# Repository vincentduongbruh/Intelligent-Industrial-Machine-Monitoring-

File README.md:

# Intelligent Industrial Motor Monitoring

**Real-Time Fault Detection Using Current, Vibration, and Temperature Sensing**

This project presents an intelligent motor health monitoring system designed to detect early-stage electrical and mechanical faults in industrial motors. The system continuously measures **3-phase current**, **vibration**, and **temperature**, analyzes these signals in real time, and visualizes motor health indicators through a graphical user interface (GUI).

The work was conducted in collaboration with **NASA Ames Research Center** and builds upon prior research on generalized fault detection using the **Filtered Park’s Vector Approach (FPVA)**. While traditional fault-detection methods often remain confined to offline analysis or simulation, this project focuses on a **deployable, sensor-driven monitoring platform** suitable for real-world industrial environments.

---

## Motivation

Induction motors account for approximately **90% of electrically driven industrial machinery**, including:
- Manufacturing robots
- CNC machines
- Conveyors
- HVAC systems
- Aerospace actuators and pumps

Despite their ubiquity, motor faults such as **bearing wear**, **shaft misalignment**, **gear damage**, and **electrical phase imbalance** often go undetected until catastrophic failure. These faults manifest as changes in:
- Current signatures
- Vibration spectra
- Operating temperature

This project bridges the gap between **fault-detection algorithms** and **physical monitoring infrastructure**, enabling early detection and improved system reliability.

---

## System Overview

The system is composed of three primary subsystems:

1. **Temperature & Vibration Sensing PCB**
2. **3-Phase Current Sensing PCB**
3. **Data Processing Server and GUI**

Sensor data is transmitted to the processing server via a combination of **USB** and **Bluetooth Low Energy (BLE)** links.

> Note: Due to limited access to industrial induction motors, testing was performed using **ESC-driven brushless motors**. While this changes the expected current waveforms, the monitoring approach remains applicable to industrial motors and VFD-driven systems.

---

## Hardware Architecture

### Sensors
- **Temperature**: Dual SHT30 temperature sensors mounted near motor windings
- **Vibration**: Dual MPU6500 IMUs measuring linear acceleration
- **Current**: Non-invasive current transformer measuring 3-phase current

### Electronics
- **ESP32 Microcontrollers**
  - One ESP32 for temperature & vibration sensing
  - One ESP32 for high-speed current acquisition

### Physical Testing Rig
- Custom **3D-printed rig** for:
  - Mechanical stability
  - Consistent sensor placement
  - Repeatable experiments

---

## Embedded Software

### Sensor Drivers
- Custom I2C drivers for temperature and IMU sensors
- Register-level configuration based on manufacturer datasheets
- Real-time data acquisition

### Sensor Calibration
- **Affine sensor model** used to correct bias and sensitivity
- Gravity-based calibration for IMUs
- Known-reference calibration for temperature sensors

### Signal Conditioning
- **Exponential Moving Average (EMA) low-pass filtering**
  - Reduces high-frequency noise
  - Lightweight and suitable for real-time embedded systems

### Communication
- **BLE (1 kHz)**: Temperature and vibration data
- **USB (10 kHz)**: Phase-accurate 3-phase current data
  - Chosen to avoid wireless latency and phase misalignment

---

## Data Processing

### Park’s Vector Approach
- Converts 3-phase currents into the rotating **d–q reference frame**
- Enables fault detection through geometric patterns in the id–iq plane

Under ideal conditions:
- Healthy motor → circular Park’s Vector trajectory
- Faulted motor → distorted or asymmetric trajectory

For ESC-driven motors:
- Healthy motor → six-pointed star pattern
- Phase fault → collapsed or triangular pattern

The system adapts the interpretation of Park’s Vector results based on the motor drive method.

---

## Graphical User Interface (GUI)

The GUI provides real-time visualization of:

1. **3-Phase Current Waveforms**
2. **Filtered Park’s Vector Plot**
3. **Vibration (Time + Frequency Domain)**
   - RMS vibration
   - FFT-based frequency analysis
4. **Temperature Monitoring**

Threshold-based alerts notify the user of potential electrical or mechanical faults.

---

## Testing and Validation

Fault conditions were intentionally introduced to validate system behavior:
- **Phase imbalance** via diode-induced waveform distortion
- **Mechanical vibration** using off-center rotating loads
- **Thermal stress** via high-throttle motor operation

The system consistently distinguished healthy and faulted operating states across current, vibration, and temperature modalities.

---

## Challenges and Limitations

- **Wireless latency** caused phase misalignment (resolved by USB current transmission)
- **ESC-driven motors** produce non-sinusoidal waveforms
- **High sampling rates** (≥10 kHz) required for accurate current analysis
- Limited access to industrial induction motors for final validation

---

## Future Work

- Deploy and validate system on industrial induction motors
- Apply machine learning for **multi-class fault classification**
- Extract higher-level features from current, vibration, and thermal data
- Improve fault localization and severity estimation

---

## Team

- **Nick Bui**
- **Mohamed Homsi**
- **Aashrith Beesabathuni**
- **Vincent Duong**
- **Carter Chen**

---

## Acknowledgements

We thank:
- Professor Dutta
- Paul De La Sayette
- Matteo Guarrera
- Dr. Rodney Martin
- Isak Bolin (NASA Ames Research Center)

for their guidance and foundational research support.

---

## References

- Bolin, I. *Generalized Fault Detection of Broken Rotor Bars in Induction Motors*, Uppsala University, 2024.

---

## To run GUI on Raspberry Pi or Laptop: 
<pre>cd src/raspberry_pi </pre>
<pre>python -m venv env</pre>
<pre>source env/bin/activate</pre>
<pre>pip install -r requirements.txt</pre>
<pre>python gui.py</pre>

## Troubleshooting FAQ:
#### BLE Connection Failing: 
- Ctrl+C to terminate
- Reset ESP 1
- <pre>python gui.py</pre>
#### CT Data Missing:
- Ctrl+C to terminate
- Reset ESP2
- <pre>python gui.py</pre>

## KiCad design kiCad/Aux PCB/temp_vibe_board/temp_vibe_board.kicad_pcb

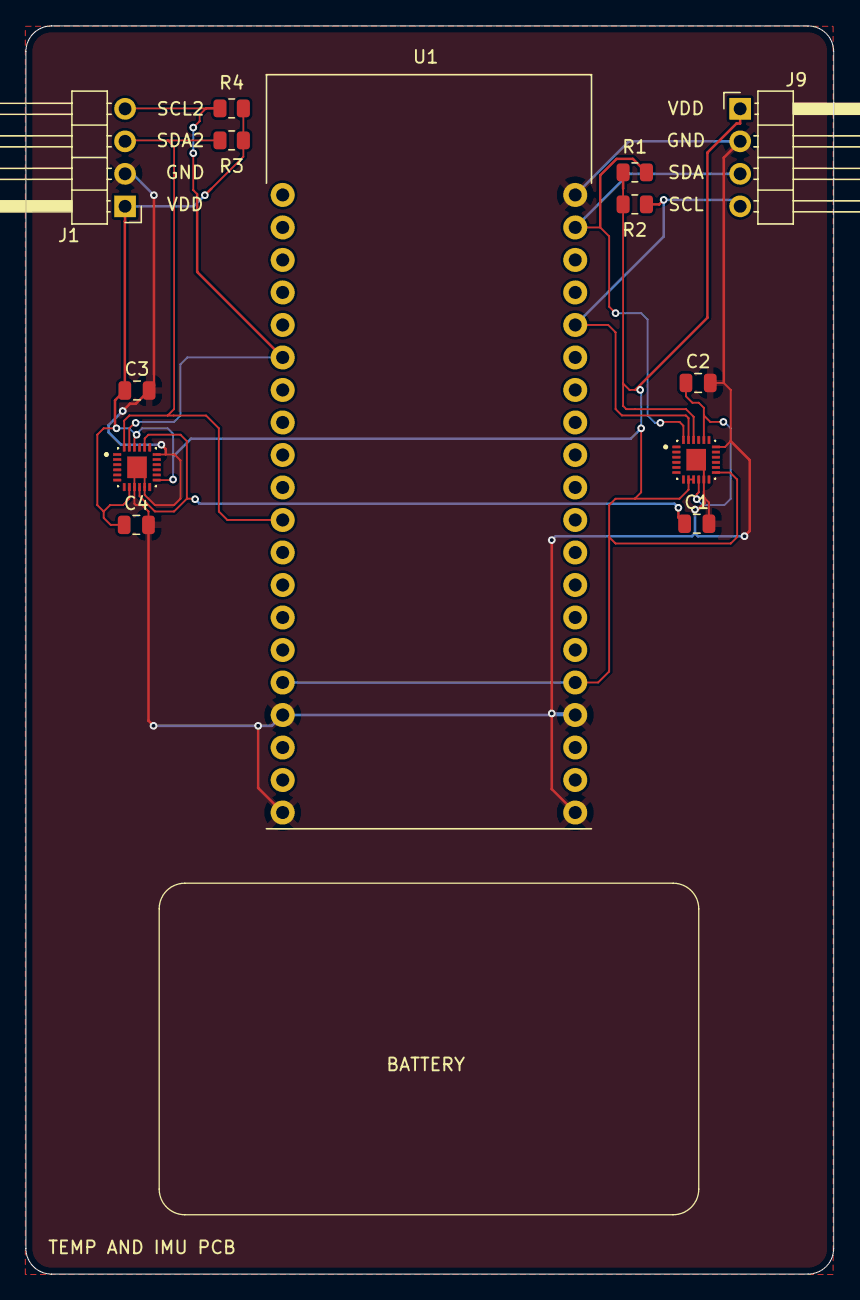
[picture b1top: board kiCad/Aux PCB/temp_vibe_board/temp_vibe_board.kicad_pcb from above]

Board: 2 copper layers, 63.1 x 97.5 mm, 13 parts (0 on the bottom side), 8 nets.

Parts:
C1, C2, C3, C4: 0.1 uF; C_0805_2012Metric
J1, J9: Conn_01x04_Pin; PinHeader_1x04_P2.54mm_Horizontal
R1, R2, R3, R4: 4.7 K; R_0805_2012Metric
U1: DEV-13907; MODULE_DEV-13907
U2, U6: MPU-6500; MPU6500

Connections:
GND: C1.2, C2.2, C3.2, C4.2, J1.2, J9.2, U1.J1_1 (GND), U1.J1_4 (GND), U1.J2_1 (GND), U1.J2_4 (GND), U1.J2_20 (GND), U2.11 (FSYNC), U2.18 (GND), U2.25 (EXP), U6.9 (AD0/SDO), U6.11 (FSYNC), U6.18 (GND), U6.25 (EXP)
unnamed: C2.1, U2.10 (REGOUT), U2.20 (RESV_2)
unnamed: C1.1, U6.10 (REGOUT), U6.20 (RESV_2)
SCL: J9.4, R1.2, U1.J2_16 (U0_RTS/V_SPI_WP/GPIO22/SCL/22), U2.23 (SCL/SCLK)
SCL2: J1.4, R4.2, U1.J1_15 (TOUCH8/ADC1_5/GPIO33/XTAL32/33), U6.23 (SCL/SCLK)
SDA: J9.3, R2.2, U1.J2_19 (V_SPI_HD/GPIO21/SDA/21), U2.24 (SDA/SDI)
SDA2: J1.3, R3.2, U1.J1_10 (TOUCH7/ADC2_7/GPIO27/27), U6.24 (SDA/SDI)
VDDIO: C3.1, C4.1, J1.1, J9.1, R1.1, R2.1, R3.1, R4.1, U1.J1_5 (3.3V/3V3), U1.J2_5 (3.3V/3V3), U2.8 (VDDIO), U2.9 (AD0/SDO), U2.13 (VDD), U2.22 (NCS), U6.8 (VDDIO), U6.13 (VDD), U6.22 (NCS)

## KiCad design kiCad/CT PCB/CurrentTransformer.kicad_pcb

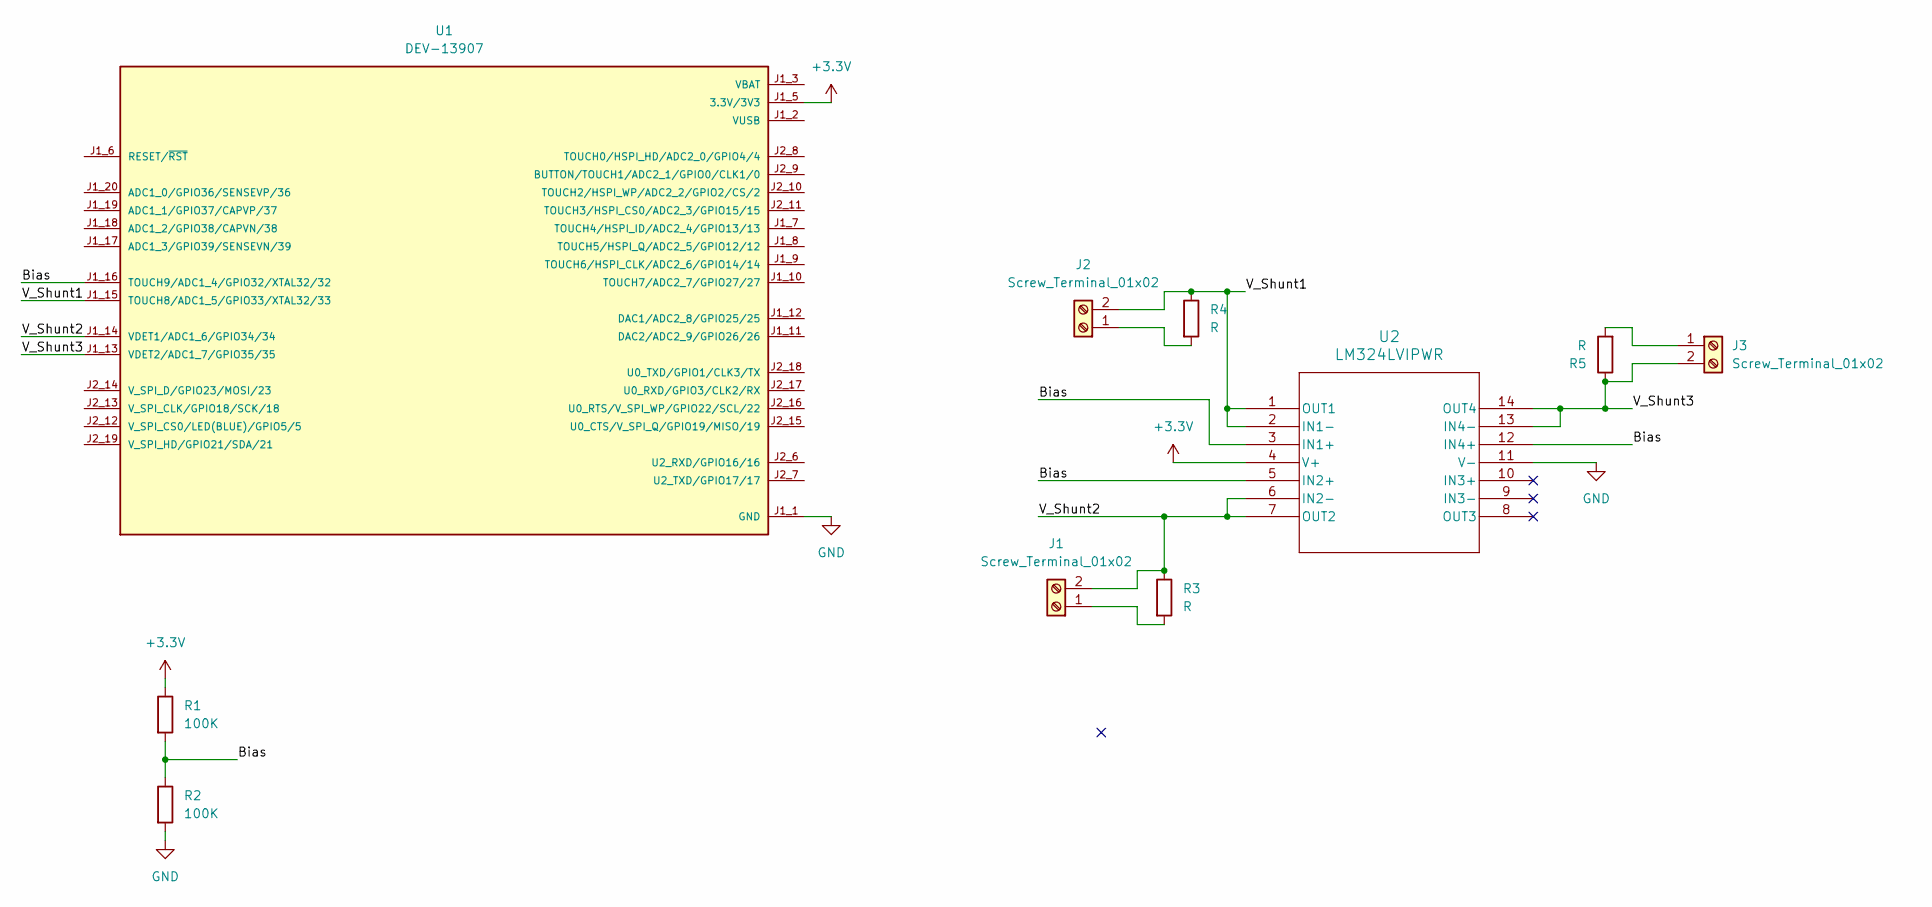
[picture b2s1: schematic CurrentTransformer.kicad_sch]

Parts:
J1, J2, J3: Screw_Terminal_01x02; OST_OSTTE020104
R1, R2: 100K; R_0603_1608Metric
R3, R4, R5: R; R_Axial_DIN0207_L6.3mm_D2.5mm_P10.16mm_Horizontal
U1: DEV-13907; MODULE_DEV-13907; PARTREV V10
U2: LM324LVIPWR; PW14_TEX-L

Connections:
+3.3V: R1.1, U1.J1_5 (3.3V/3V3), U1.J2_5 (3.3V/3V3), U2.4 (V+)
/Bias: R1.2, R2.1, U1.J1_16 (TOUCH9/ADC1_4/GPIO32/XTAL32/32), U2.3 (IN1+), U2.5 (IN2+), U2.12 (IN4+)
/V_Shunt1: J2.2, R4.1, U1.J1_15 (TOUCH8/ADC1_5/GPIO33/XTAL32/33), U2.1 (OUT1), U2.2 (IN1-)
/V_Shunt2: J1.2, R3.1, U1.J1_14 (VDET1/ADC1_6/GPIO34/34), U2.6 (IN2-), U2.7 (OUT2)
/V_Shunt3: J3.2, R5.1, U1.J1_13 (VDET2/ADC1_7/GPIO35/35), U2.13 (IN4-), U2.14 (OUT4)
GND: R2.2, U1.J1_1 (GND), U1.J1_4 (GND), U1.J2_1 (GND), U1.J2_4 (GND), U1.J2_20 (GND), U2.11 (V-)
unnamed: J1.1, R3.2
unnamed: J2.1, R4.2
unnamed: J3.1, R5.2
VBAT: U1.J1_3 (VBAT), U1.J2_3 (VBAT)
VUSB: U1.J1_2 (VUSB), U1.J2_2 (VUSB)

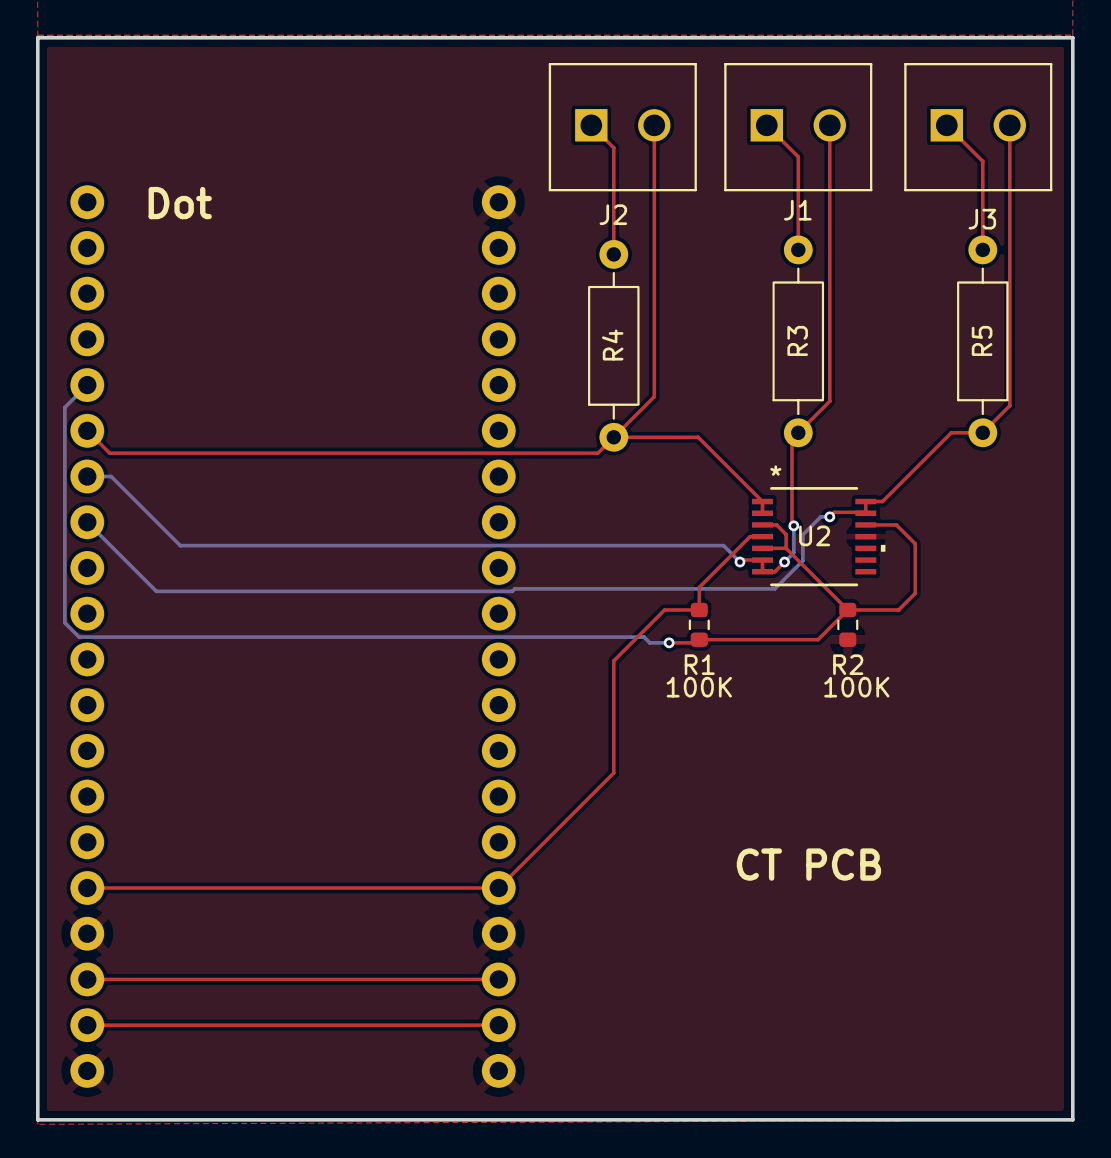
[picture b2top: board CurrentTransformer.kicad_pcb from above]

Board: 2 copper layers, 57.5 x 60.1 mm, 10 parts (1 on the bottom side), 11 nets.

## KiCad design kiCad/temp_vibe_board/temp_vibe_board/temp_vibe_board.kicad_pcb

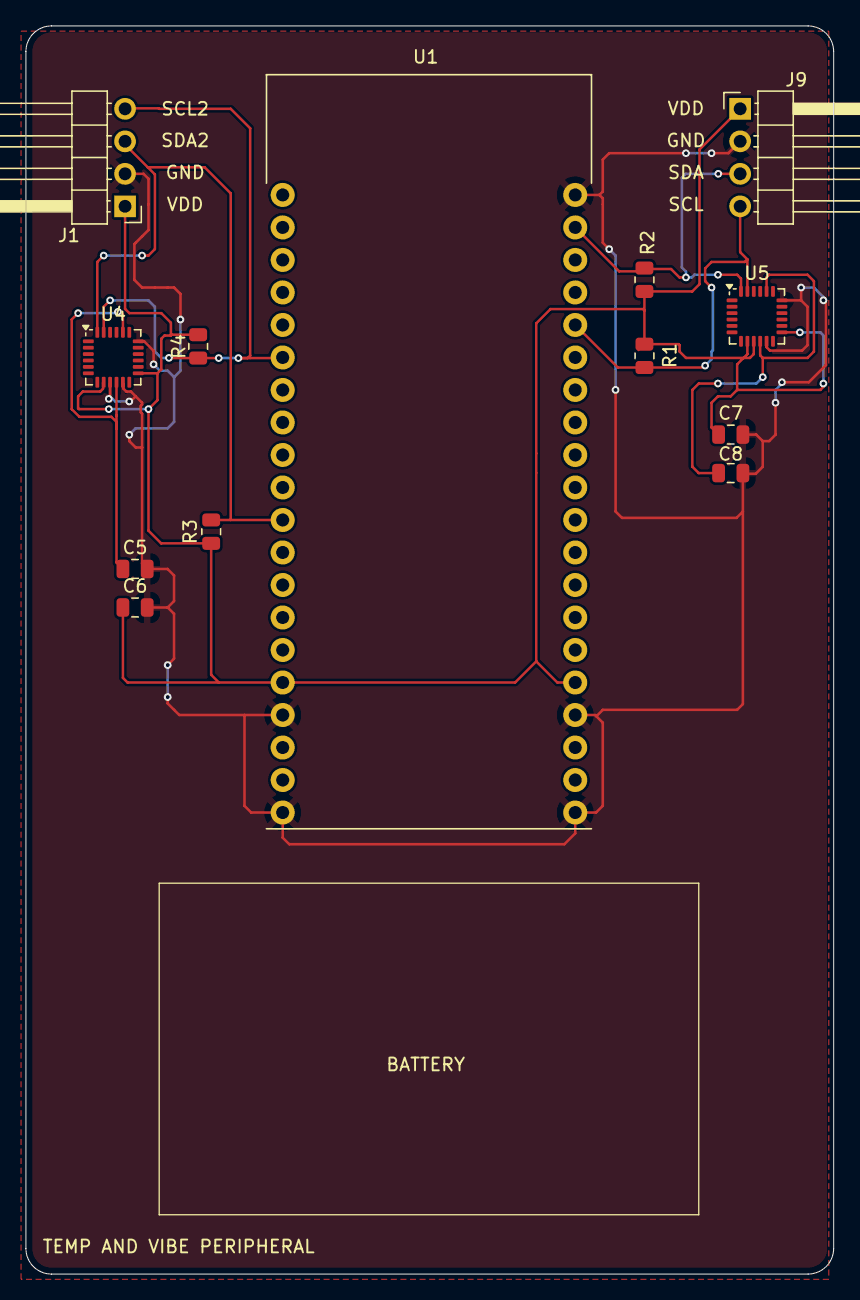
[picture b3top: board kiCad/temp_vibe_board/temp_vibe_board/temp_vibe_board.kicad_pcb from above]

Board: 2 copper layers, 63.1 x 97.5 mm, 13 parts (0 on the bottom side), 8 nets.

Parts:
C5, C6, C7, C8: 0.1 uF; C_0805_2012Metric
J1, J9: Conn_01x04_Pin; PinHeader_1x04_P2.54mm_Horizontal
R1, R2, R3, R4: 4.7 K; R_0805_2012Metric
U1: DEV-13907; MODULE_DEV-13907
U4, U5: MPU-6050; InvenSense_QFN-24_4x4mm_P0.5mm

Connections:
GND: C5.2, C6.2, C7.2, C8.2, J1.2, J9.2, U1.J1_1 (GND), U1.J1_4 (GND), U1.J2_1 (GND), U1.J2_4 (GND), U1.J2_20 (GND), U4.9 (AD0), U4.11 (FSYNC), U4.18 (GND), U5.11 (FSYNC), U5.18 (GND)
unnamed: C5.1, U4.10 (REGOUT), U4.20 (CPOUT)
unnamed: C8.1, U5.10 (REGOUT), U5.20 (CPOUT)
SCL: J9.4, R1.2, U1.J2_16 (U0_RTS/V_SPI_WP/GPIO22/SCL/22), U5.23 (SCL)
SCL2: J1.4, R4.2, U1.J1_15 (TOUCH8/ADC1_5/GPIO33/XTAL32/33), U4.23 (SCL)
SDA: J9.3, R2.2, U1.J2_19 (V_SPI_HD/GPIO21/SDA/21), U5.24 (SDA)
SDA2: J1.3, R3.2, U1.J1_10 (TOUCH7/ADC2_7/GPIO27/27), U4.24 (SDA)
VDDIO: C6.1, C7.1, J1.1, J9.1, R1.1, R2.1, R3.1, R4.1, U1.J1_5 (3.3V/3V3), U1.J2_5 (3.3V/3V3), U4.8 (VLOGIC), U4.13 (VDD), U5.8 (VLOGIC), U5.9 (AD0), U5.13 (VDD)

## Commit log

2025-11-11 MPU6050
2025-11-13 MPU 9250
2025-11-13 Current Transformer
2025-11-13 SHT30
2025-11-14 Temp and Accelerometer Integrated
2025-11-19 CT ESP Folder Fix
2025-11-23 temp_vibe_board_v1
2025-11-23 Add files via upload
    CT
2025-11-23 Rename kiCad/CurrentTransformer-B_Cu.gbr to kiCad/CT/CurrentTransformer-B_Cu.gbr
2025-11-23 Rename kiCad/CurrentTransformer-B_Mask.gbr to kiCad/CT/CurrentTransformer-B_Mask.gbr
2025-11-23 Rename kiCad/CurrentTransformer-B_Paste.gbr to kiCad/CT/CurrentTransformer-B_Paste.gbr
2025-11-23 Rename kiCad/CurrentTransformer-B_Silkscreen.gbr to kiCad/CT/CurrentTransformer-B_Silkscreen.gbr
2025-11-23 Rename kiCad/CurrentTransformer-F_Mask.gbr to kiCad/CT/CurrentTransformer-F_Mask.gbr
2025-11-23 Rename kiCad/CurrentTransformer-F_Cu.gbr to kiCad/CT/CurrentTransformer-F_Cu.gbr
2025-11-23 Rename kiCad/CurrentTransformer-Edge_Cuts.gbr to kiCad/CT/CurrentTransformer-Edge_Cuts.gbr
2025-11-23 Rename kiCad/CurrentTransformer-F_Silkscreen.gbr to kiCad/CT/CurrentTransformer-F_Silkscreen.gbr
2025-11-23 Rename kiCad/CurrentTransformer-F_Paste.gbr to kiCad/CT/CurrentTransformer-F_Paste.gbr
2025-11-23 Rename kiCad/CurrentTransformer.kicad_pcb to kiCad/CT/CurrentTransformer.kicad_pcb
2025-11-23 Rename kiCad/CurrentTransformer.kicad_prl to kiCad/CT/CurrentTransformer.kicad_prl
2025-11-23 Rename kiCad/CurrentTransformer-job.gbrjob to kiCad/CT/CurrentTransformer-job.gbrjob
2025-11-23 Rename kiCad/fp-info-cache to kiCad/CT/fp-info-cache
2025-11-23 Rename kiCad/CurrentTransformer.kicad_sch to kiCad/CT/CurrentTransformer.kicad_sch
2025-11-23 Rename kiCad/CurrentTransformer.kicad_pro to kiCad/CT/CurrentTransformer.kicad_pro
2025-11-24 Rename kiCad/CThere.zip to kiCad/CurrentTransformer/CThere.zip
2025-11-25 updated_temp_vibe_board
2025-11-25 MPU6050 PCB
2025-11-26 fixed sch
2025-11-27 updated CT code for multiple CTs
2025-12-01 experimented with BLE for esp1 and rpi, changed int16 to float
2025-12-02 Integrating BT and Setting Up BTHandler
2025-12-03 ESPNOW
2025-12-03 MPU9250 Calibration and Integration
2025-12-03 Added EMA LP Filtering and Integrated into IMU and Temp Reads
2025-12-03 implemented FOC equations
2025-12-04 AUX PCB Upload
2025-12-04 PCB files
2025-12-09 Testing ESP1
2025-12-09 debug sensor data
2025-12-09 Fixed Firmware ESP1
2025-12-09 working on integrating espnow transmitter and receiver
2025-12-09 EMA Works
2025-12-09 Temp Calib
2025-12-10 Debuggin I2C and Clean Up
2025-12-11 fix merge conflicts
2025-12-12 Resolved Merge Conflicts
2025-12-12 ESP1 Debugging
2025-12-14 finish GUI
2025-12-14 esp2_adc_driver
2025-12-14 imu_temp_vibe_working
2025-12-14 2temp_1IMU_working
2025-12-15 Working on ESPNOW
2025-12-15 E2E ESPNow and BLE Tested and Working
2025-12-15 First E2E Success
2025-12-17 fixed gui issues
2025-12-17 Integrated CT Read into ESP2
2025-12-17 Debugging E2E
2025-12-17 Serial
2025-12-17 switching to uart
2025-12-17 working uart
2025-12-17 merging from test_paper
2025-12-17 Debugging GUI
2025-12-17 ESP 2
2025-12-18 Working GUI
2025-12-18 added dataframe to csv
2025-12-18 test
2025-12-18 data
2025-12-18 dataset
2025-12-18 minor changes
2025-12-18 new df to csv
2025-12-18 more data
2025-12-18 E2E done
2025-12-18 warningsys_logo
2025-12-18 test_motor_rpm
2025-12-18 motor_swtich
2025-12-18 test changes
2025-12-18 attempt at interpolation
2025-12-18 attempt to fit sine curve
2025-12-18 fixed bias reading
2025-12-18 tweaked df to csv method in main.py
2025-12-18 tweaked df to csv method in main
2025-12-18 GUI Working, CSV for Processing
2025-12-18 10 KHz
2025-12-18 Diode Motor Fault
2025-12-18 Diode Fault
2025-12-18 Line -> Scatter for GUI
2025-12-18 README
